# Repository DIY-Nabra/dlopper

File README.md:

Dlopper
=======

This is the Dlopper, a control circuit.

It outputs gates and control voltage due to light differentials.

Download the PDF from [here](assets/dlopper.pdf)

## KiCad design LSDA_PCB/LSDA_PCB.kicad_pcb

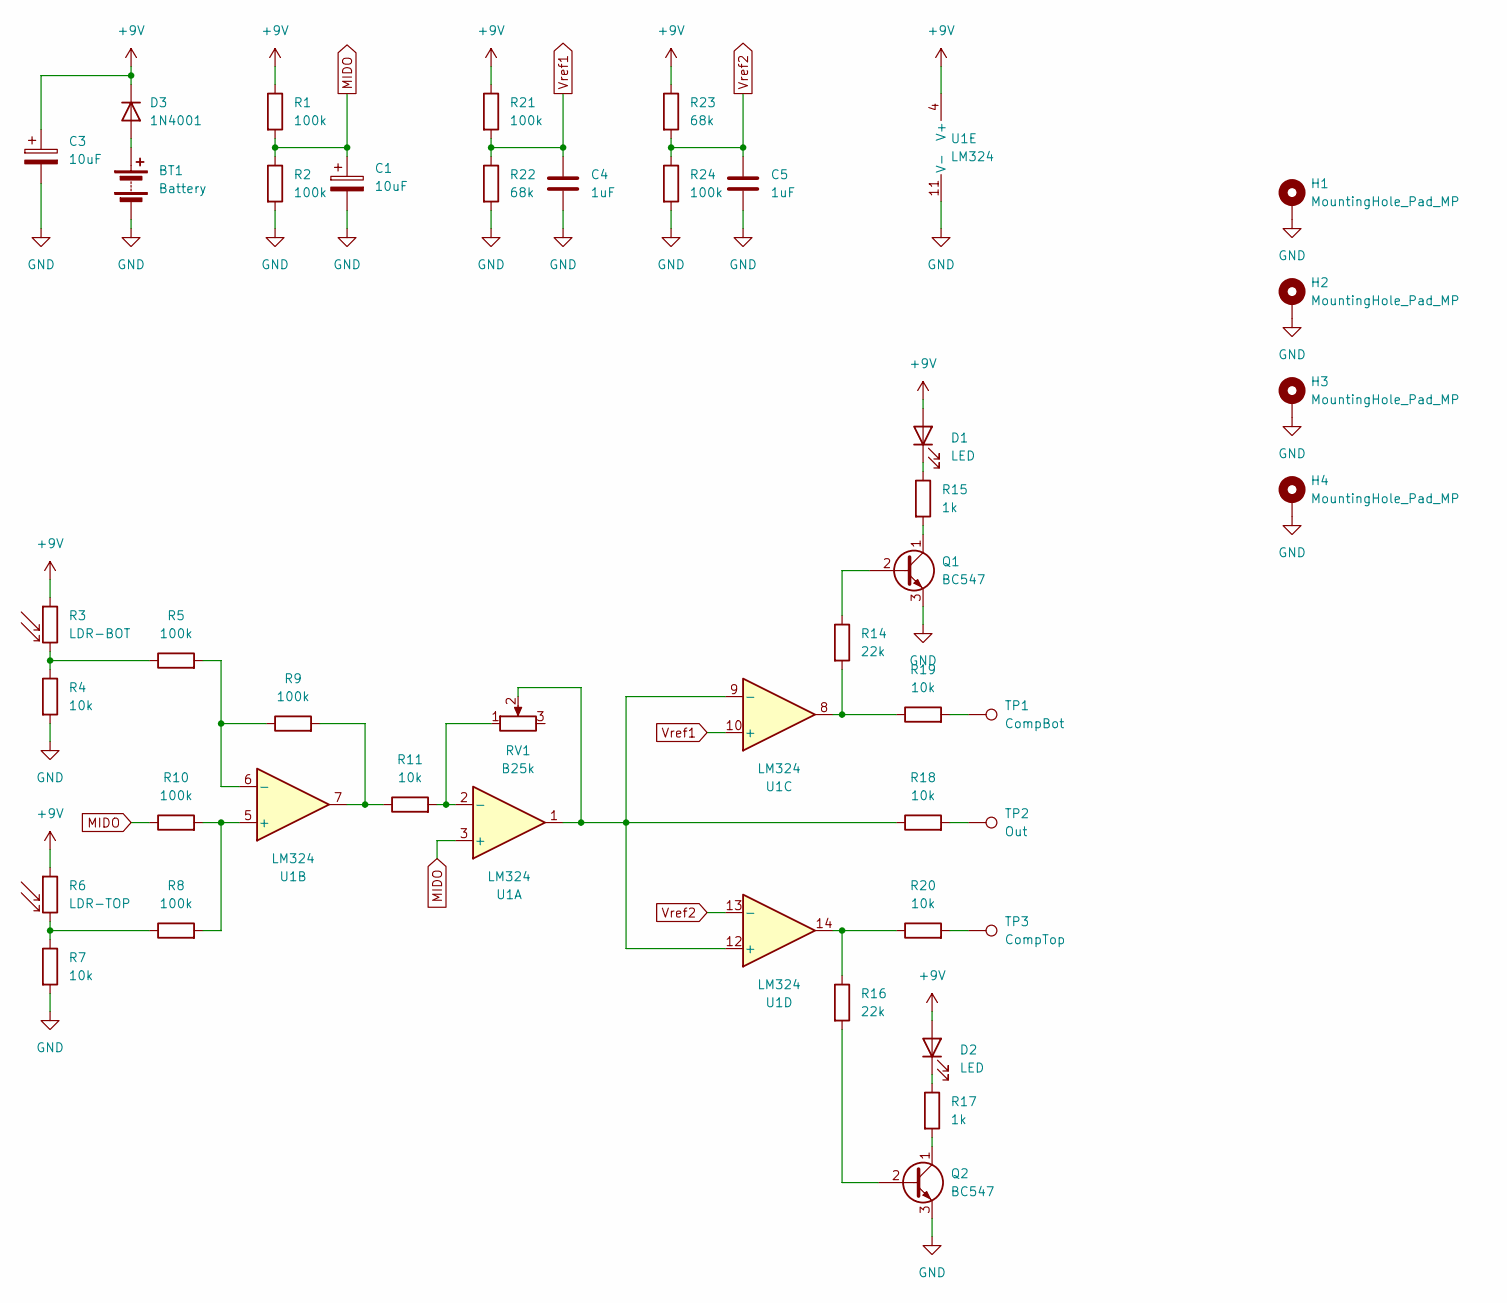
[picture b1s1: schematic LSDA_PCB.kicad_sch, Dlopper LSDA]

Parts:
BT1: Battery; wobelisk
C1, C3: 10uF; cel1
C4, C5: 1uF; cpoly105
D1, D2: LED; led
D3: 1N4001; power-1n4001
H1, H2, H3, H4: MountingHole_Pad_MP; MountingHole_3.2mm_M3_ISO7380_Pad
Q1, Q2: BC547; qnpn
R1, R2, R5, R8, R9, R10, R21, R24: 100k; r3
R3: LDR-BOT; cadsulfide_sm
R4, R7, R11, R18, R19, R20: 10k; r3
R6: LDR-TOP; cadsulfide_sm
R14, R16: 22k; r3
R15, R17: 1k; r3
R22, R23: 68k; r3
RV1: B25k; wnob
TP1: CompBot; wsqout
TP2: Out; wsqout
TP3: CompTop; wsqout
U1: LM324; dip14

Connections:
+9V: C3.1, D1.2 (A), D2.2 (A), D3.1 (K), R1.1, R3.1, R6.1, R21.1, R23.1, U1.4 (V+)
GND: BT1.2 (-), C1.2, C3.2, C4.2, C5.2, H1.MP, H2.MP, H3.MP, H4.MP, Q1.3 (E), Q2.3 (E), R2.2, R4.2, R7.2, R22.2, R24.2, U1.11 (V-)
MIDO: C1.1, R1.2, R2.1, R10.1, U1.3 (+)
unnamed: BT1.1 (+), D3.2 (A)
unnamed: D1.1 (K), R15.1
unnamed: D2.1 (K), R17.1
unnamed: Q1.2 (B), R14.1
unnamed: Q1.1 (C), R15.2
unnamed: Q2.2 (B), R16.2
unnamed: Q2.1 (C), R17.2
unnamed: R3.2, R4.1, R5.1
unnamed: R6.2, R7.1, R8.1
unnamed: R9.2, R11.1, U1.7
unnamed: R14.2, R19.1, U1.8
unnamed: R16.1, R20.1, U1.14
unnamed: R18.2, TP2.1
unnamed: R19.2, TP1.1
unnamed: R20.2, TP3.1
unnamed: R11.2, RV1.1, U1.2 (-)
unnamed: R8.2, R10.2, U1.5 (+)
unnamed: R5.2, R9.1, U1.6 (-)
unnamed: R18.1, RV1.2, U1.1, U1.9 (-), U1.12 (+)
Vref1: C4.1, R21.2, R22.1, U1.10 (+)
Vref2: C5.1, R23.2, R24.1, U1.13 (-)

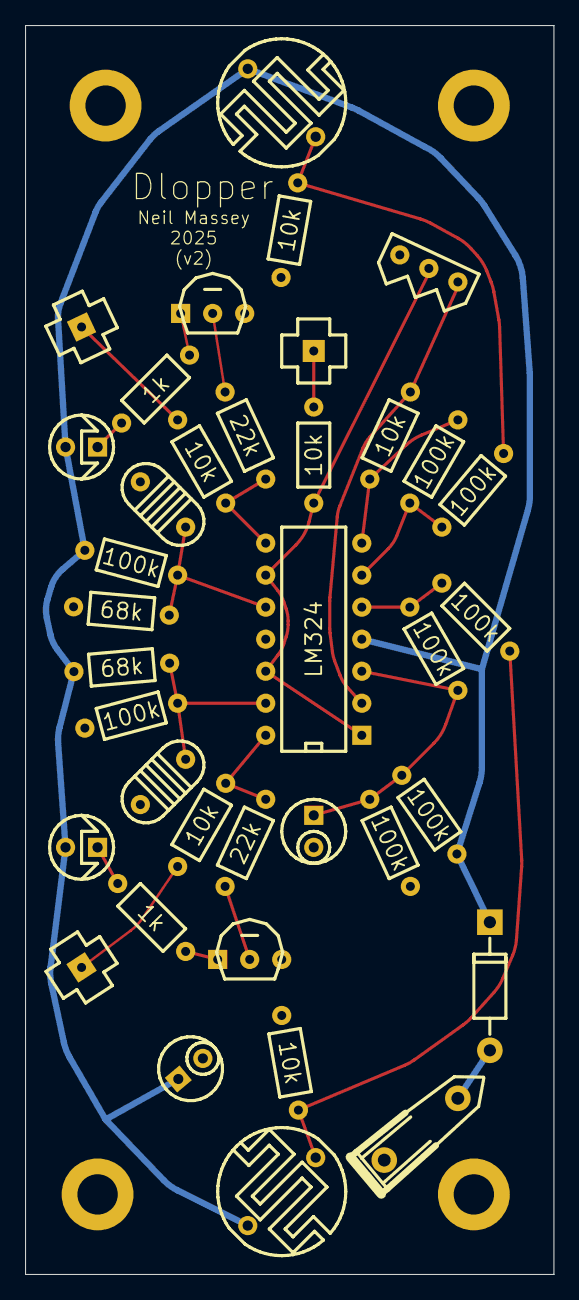
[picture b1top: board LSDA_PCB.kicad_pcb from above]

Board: 2 copper layers, 41.9 x 99.1 mm, 41 parts (0 on the bottom side), 24 nets.

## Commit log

2025-02-04 Added PDF link
2025-02-07 Added schematic
2025-02-08 Revision 2
2025-02-08 Fixed broken track
2025-02-09 Created paper and PCB versions
2025-02-09 Removed backups
2025-02-09 Cleaning up
2025-02-10 Updated LED footprints - thanks Josh
2025-04-19 PCB version
2025-04-19 Updated footprints
2025-04-19 Mounting holes
